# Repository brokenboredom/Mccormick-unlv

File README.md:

Name: Samuel McCormick  
NSHE: 1014303276  
Email: samuel.mccormick@gmail.com

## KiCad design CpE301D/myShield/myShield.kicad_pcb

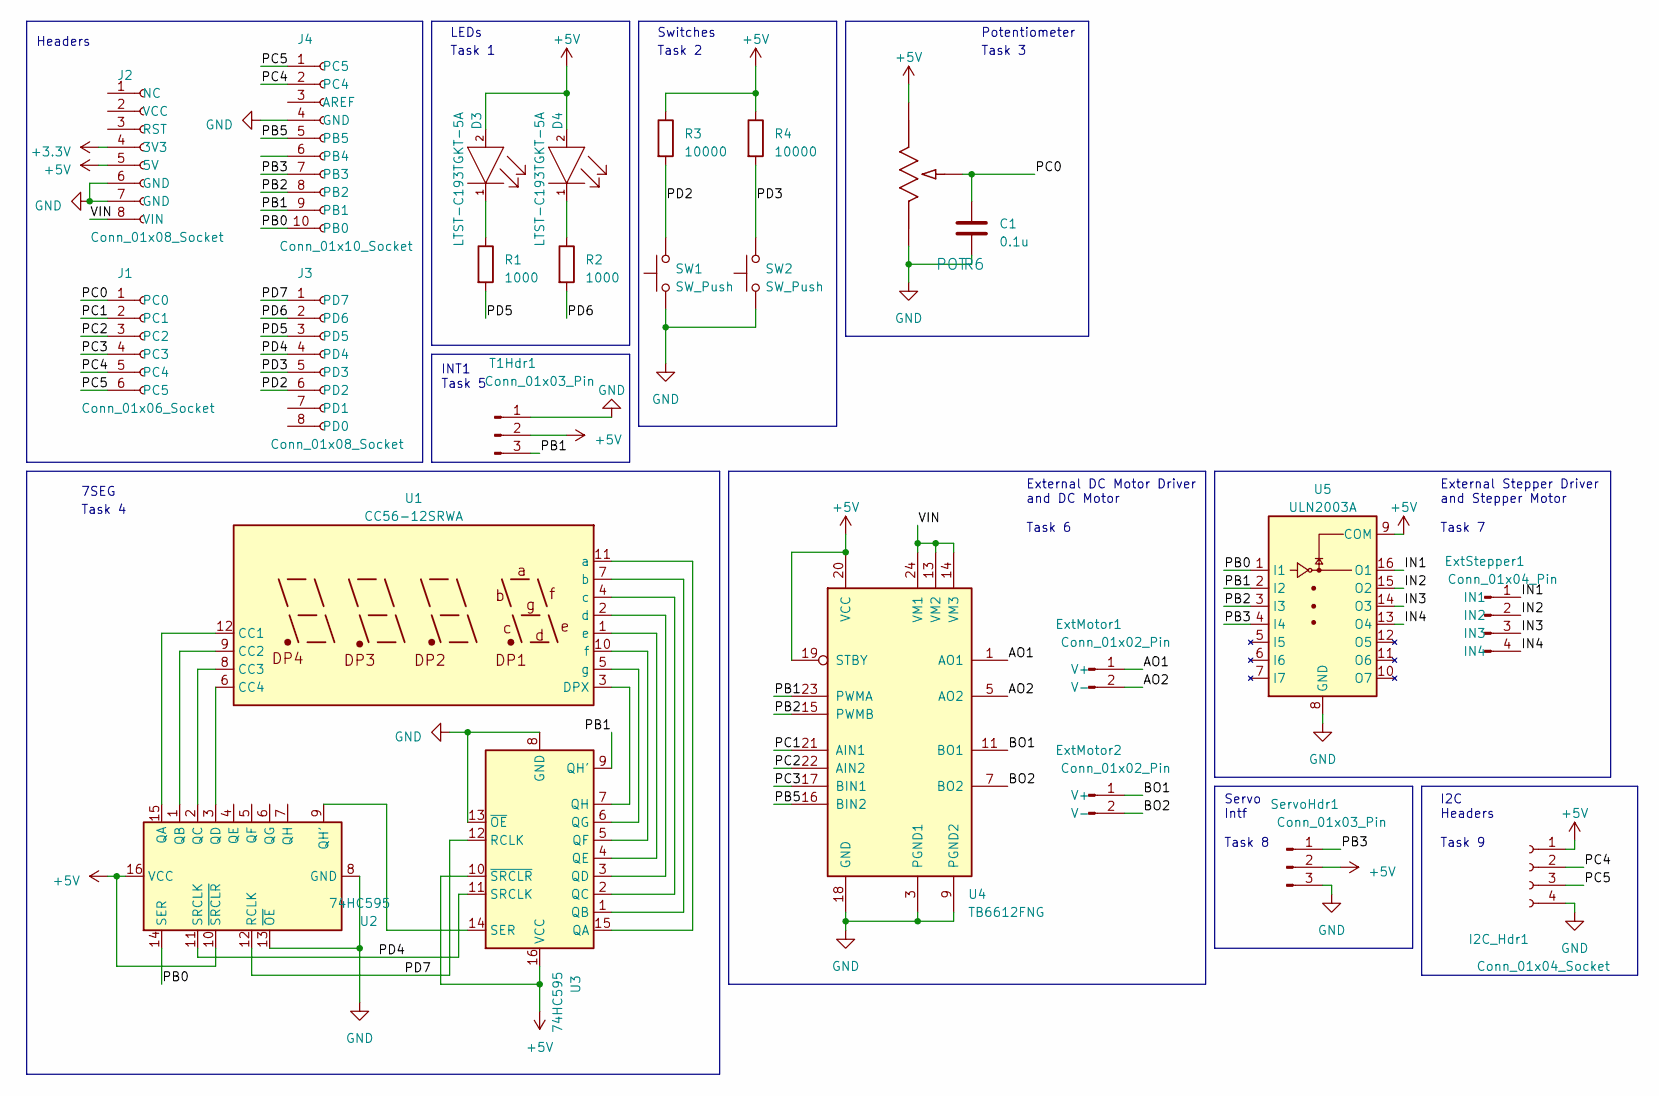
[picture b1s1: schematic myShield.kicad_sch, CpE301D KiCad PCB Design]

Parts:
C1: 0.1u; C_0201_0603Metric
D3, D4: LTST-C193TGKT-5A; Lite-On-LTST-C193TGKT-5A-MFG; forward voltage 3.1V; reverse voltage 5V; mouser part number 859-LTSTC193TGKT5A; digikey description LED GREEN CLEAR CHIP SMD
ExtMotor1, ExtMotor2: Conn_01x02_Pin; PinHeader_1x02_P2.54mm_Vertical
ExtStepper1: Conn_01x04_Pin; PinHeader_1x04_P2.54mm_Vertical
I2C_Hdr1: Conn_01x04_Socket; PinSocket_1x04_P2.54mm_Vertical
J1: Conn_01x06_Socket; PinSocket_1x06_P2.54mm_Vertical
J2, J3: Conn_01x08_Socket; PinSocket_1x08_P2.54mm_Vertical
J4: Conn_01x10_Socket; PinSocket_1x10_P2.54mm_Vertical
R1, R2: 1000; RC0603JR-071KL
R3, R4: 10000; R_0201_0603Metric
R6: POT; 3362P-1-103LF
SW1, SW2: SW_Push; 8-1437565-1
ServoHdr1: Conn_01x03_Pin; PinHeader_1x03_P2.54mm_Vertical
T1Hdr1: Conn_01x03_Pin; PinHeader_1x03_P2.54mm_Vertical
U1: CC56-12SRWA; CA56-12SRWA
U2, U3: 74HC595; SN74HC595DWR
U4: TB6612FNG; TB6612FNG_C_8_EL
U5: ULN2003A

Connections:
+3.3V: J2.4 (3V3)
+5V: D3.2 (ANODE), D4.2 (ANODE), I2C_Hdr1.1, J2.5 (5V), R3.1, R4.1, R6.3, ServoHdr1.2, T1Hdr1.2, U2.10 (~SRCLR), U2.16 (VCC), U3.10 (~SRCLR), U3.16 (VCC), U4.19 (STBY), U4.20 (VCC), U5.9 (COM)
/AO1: ExtMotor1.1 (V+), U4.1 (AO1), U4.2 (AO1)
/AO2: ExtMotor1.2 (V-), U4.5 (AO2), U4.6 (AO2)
/BO1: ExtMotor2.1 (V+), U4.11 (BO1), U4.12 (BO1)
/BO2: ExtMotor2.2 (V-), U4.7 (BO2), U4.8 (BO2)
/IN1: ExtStepper1.1 (IN1), U5.16 (O1)
/IN2: ExtStepper1.2 (IN2), U5.15 (O2)
/IN3: ExtStepper1.3 (IN3), U5.14 (O3)
/IN4: ExtStepper1.4 (IN4), U5.13 (O4)
/PB0: J4.10 (PB0), U2.14 (SER), U5.1 (I1)
/PB1: J4.9 (PB1), T1Hdr1.3, U3.9 (QH'), U4.23 (PWMA), U5.2 (I2)
/PB2: J4.8 (PB2), U4.15 (PWMB), U5.3 (I3)
/PB3: J4.7 (PB3), ServoHdr1.1, U5.4 (I4)
/PB5: J4.5 (PB5), U4.16 (BIN2)
/PC0: C1.1, J1.1 (PC0), R6.2
/PC1: J1.2 (PC1), U4.21 (AIN1)
/PC2: J1.3 (PC2), U4.22 (AIN2)
/PC3: J1.4 (PC3), U4.17 (BIN1)
/PC4: I2C_Hdr1.2, J1.5 (PC4), J4.2 (PC4)
/PC5: I2C_Hdr1.3, J1.6 (PC5), J4.1 (PC5)
/PD2: J3.6 (PD2), R3.2, SW1.2
/PD3: J3.5 (PD3), R4.2, SW2.2
/PD4: J3.4 (PD4), U2.11 (SRCLK), U3.11 (SRCLK)
/PD5: J3.3 (PD5), R1.2
/PD6: J3.2 (PD6), R2.2
/PD7: J3.1 (PD7), U2.12 (RCLK), U3.12 (RCLK)
/VIN: J2.8 (VIN), U4.13 (VM2), U4.14 (VM3), U4.24 (VM1)
GND: C1.2, I2C_Hdr1.4, J2.6 (GND), J2.7 (GND), J4.4 (GND), R6.1, SW1.1, SW2.1, ServoHdr1.3, T1Hdr1.1, U2.8 (GND), U2.13 (~OE), U3.8 (GND), U3.13 (~OE), U4.3 (PGND1), U4.4 (PGND1), U4.9 (PGND2), U4.10 (PGND2), U4.18 (GND), U5.8 (GND)
unnamed: D3.1 (CATHODE), R1.1
unnamed: D4.1 (CATHODE), R2.1
unnamed: U1.12 (CC1), U2.15 (QA)
unnamed: U1.9 (CC2), U2.1 (QB)
unnamed: U1.8 (CC3), U2.2 (QC)
unnamed: U1.6 (CC4), U2.3 (QD)
unnamed: U1.3 (DPX), U3.7 (QH)
unnamed: U1.11 (a), U3.15 (QA)
unnamed: U1.7 (b), U3.1 (QB)
unnamed: U1.4 (c), U3.2 (QC)
unnamed: U1.2 (d), U3.3 (QD)
unnamed: U1.1 (e), U3.4 (QE)
unnamed: U1.10 (f), U3.5 (QF)
unnamed: U1.5 (g), U3.6 (QG)
unnamed: U2.9 (QH'), U3.14 (SER)

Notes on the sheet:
External DC Motor Driver and DC Motor Task 6
Switches
Task 2
Servo Intf Task 8
Task 3
7SEG
I2C Headers Task 9
Potentiometer
External Stepper Driver and Stepper Motor Task 7
INT1 Task 5
Task 4
Headers
Task 1
LEDs

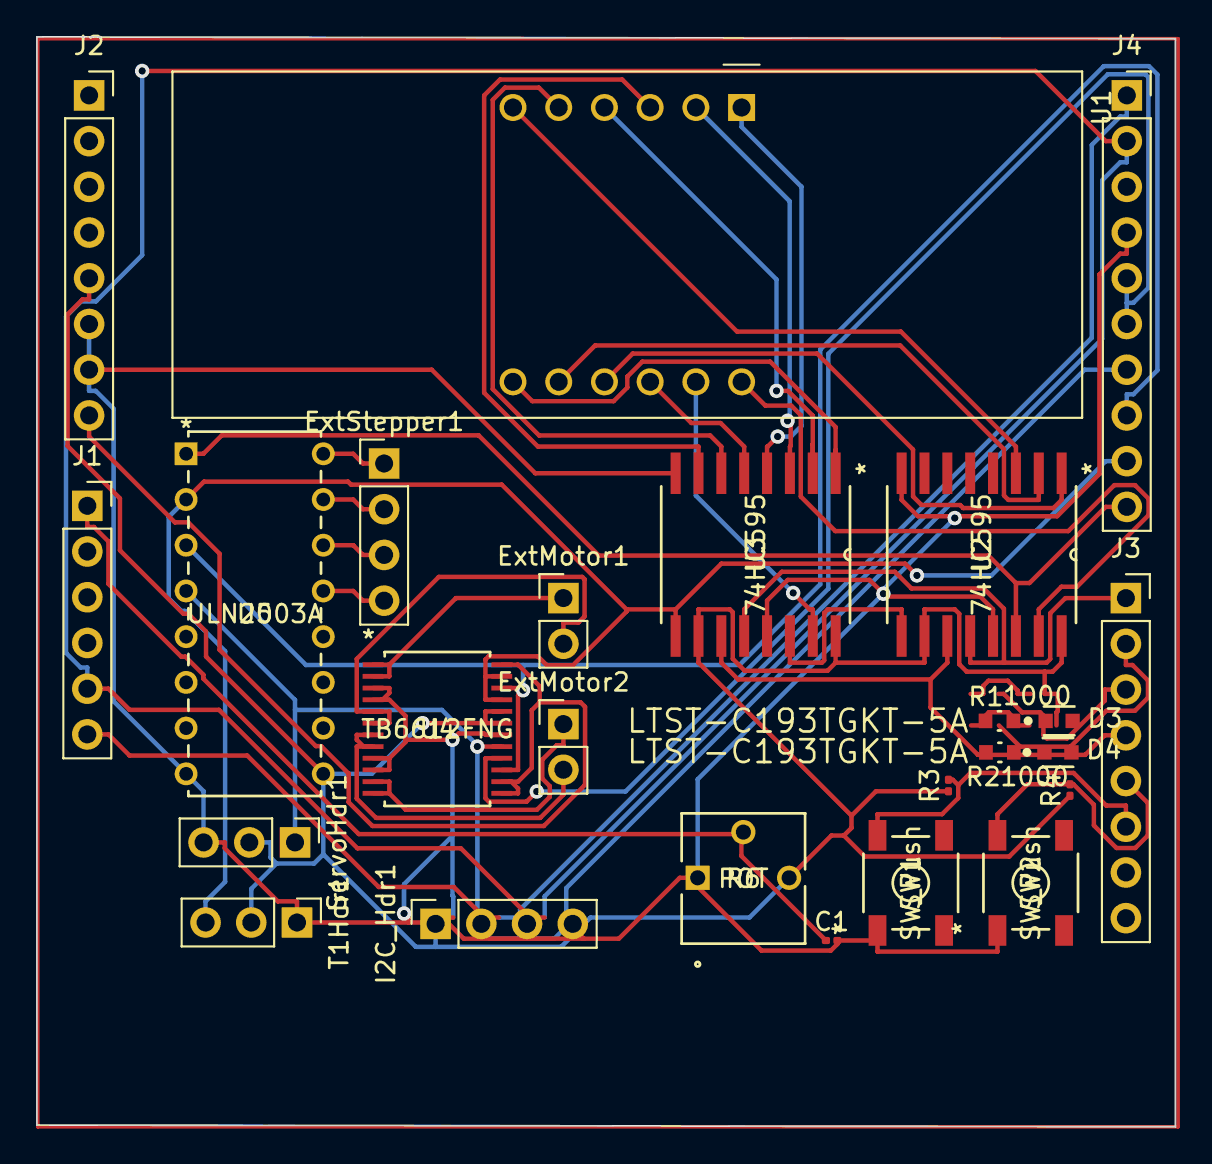
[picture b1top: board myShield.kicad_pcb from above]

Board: 2 copper layers, 63.2 x 60.5 mm, 25 parts (0 on the bottom side), 43 nets.

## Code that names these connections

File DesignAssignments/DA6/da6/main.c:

/*
 * da6.c
 *
 * Created: 4/13/2023 7:54:39 AM
 * Author : samue
 */ 

//-------------------------------------------------------------------------
#define F_CPU 16000000UL

#include <avr/io.h>
#include <util/delay.h>
#include <avr/interrupt.h>
#include <stdio.h>
#define BAUDRATE 9600
#define BAUD_PRESCALLER (((F_CPU / (BAUDRATE * 16UL))) - 1)
//-------------------------------------------------------------------------------

#define SHIFT_REGISTER DDRB
#define SHIFT_PORT PORTB
#define DATA (1<<PB3)		//MOSI (SI)
#define LATCH (1<<PB2)		//SS   (RCK)
#define CLOCK (1<<PB5)		//SCK  (SCK)

void read_adc(void);
void adc_init(void);
void init_IO(void){
	//Setup IO
	SHIFT_REGISTER |= (DATA | LATCH | CLOCK);	//Set control pins as outputs
	SHIFT_PORT &= ~(DATA | LATCH | CLOCK);		//Set control pins low
}
void init_SPI(void){
	//Setup SPI
	SPCR = (1<<SPE) | (1<<MSTR);	//Start SPI as Master
}
void spi_send(unsigned char byte){
	SPDR = byte;			//Shift in some data
	while(!(SPSR & (1<<SPIF)));	//Wait for SPI process to finish
}

/* Segment byte maps for numbers 0 to 9 */
const uint8_t SEGMENT_MAP[] = {0xC0, 0xF9, 0xA4, 0xB0, 0x99,
									0x92, 0x82, 0xF8, 0X80, 0X90};
/* Byte maps to select digit 1 to 4 */
const uint8_t SEGMENT_SELECT[] = {0xF1, 0xF2, 0xF4, 0xF8};
	
volatile unsigned int adc_temp;
volatile unsigned int adc_hundreds;
volatile unsigned int adc_tens;
volatile unsigned int adc_ones;
volatile int j = 4;

int main(void)
{
    //Configure TIMER2
	TCCR0A |=	(1 << COM0B1) |								// Fast PWM mode non-inverting (OC0B )
				(1 << WGM01) | (1 << WGM00);				// Fast PWM, TOP: 0xFF
	TCCR0B |=	(1 << CS02) | (1 << CS01) | (1 << CS00);	// 1024 prescaler

	//Motor test configure
	DDRD |= 0x03;		// PORTD 0 and 1 as Output
	DDRD |= (1<<PD5);	// PD5(OC0B) motor enable
	PORTD = 0x01;		// set motor to run
    adc_init();			// Initialize ADC
	init_IO();			// Setup IO ports
	init_SPI();			// Initialize SPI as master
    ADCSRA |= (1<<ADSC); //trigger
    _delay_ms(125);
    sei();				// set global interrupts

    while (1) {
	    

    }
}



void adc_init(void)
{
	ADMUX |= (0 << REFS1) |  // Voltage reference bits
	(1 << REFS0) |
	(0 << ADLAR) |  // Left adjust
	(0 << MUX3 ) |  // Source selector
	(0 << MUX2) |
	(0 << MUX1) |	// Select ADC0 (PC0) also our POT
	(0 << MUX0);
	ADCSRA |= (1 << ADEN) | //Enable ADC
	(0 << ADSC) |           //Start conversion
	(1 << ADATE) |          //Enable auto trigger
	(0 << ADIF) |           //Interrupt flag
	(1 << ADIE) |           //Enable interrupt
	(1 << ADPS2) |          //Prescalar
	(0 << ADPS1) |
	(1 << ADPS0);
	ADCSRB |= (0 << ADTS2) |  //Auto-trigger source
	(0 << ADTS1) |
	(0 << ADTS0);
}

//ADC conversion complete ISR
ISR(ADC_vect)
{
	adc_temp += ADC; //sum
	j--;
	if (j==1)
	{
		adc_temp /= 16; // 0-1023 / 16 = 0-255 / 4 average
		// This adc value from POT on protoshield should set our DC PWM duty cycle
		// So this reading needs to be translated to OCR1A
		OCR0B = adc_temp;	// Overflow will just start from 0%
		adc_temp = 0;
		j = 4;

		//Pull LATCH low (Important: this is necessary to start the SPI transfer!)
		SHIFT_PORT &= ~LATCH;

		// Extract our ADC digits
		adc_hundreds = adc_temp % 100;
		adc_temp = adc_temp - (adc_hundreds * 100)
		adc_tens = adc_temp % 10;
		adc_temp = adc_temp - (adc_tens * 10)
		adc_ones = adc_temp
		spi_send((unsigned char)SEGMENT_MAP[adc_hundreds]);
		spi_send((unsigned char)0xF2);
		spi_send((unsigned char)SEGMENT_MAP[adc_tens]);
		spi_send((unsigned char)0xF4);
		spi_send((unsigned char)SEGMENT_MAP[adc_ones]);
		spi_send((unsigned char)0xF8);
		//Toggle latch to copy data to the storage register
		SHIFT_PORT |= LATCH;
		SHIFT_PORT &= ~LATCH;
		//wait for a little bit before repeating everything
		_delay_ms(125);
	}
}

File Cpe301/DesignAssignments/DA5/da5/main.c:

/*
 * da5.c
 *
 * Created: 4/12/2023 5:50:19 PM
 * Author : Samuel McCormick
 */ 
//-------------------------------------------------------------------------
#define F_CPU 16000000UL

#include <stdio.h>
#include <stdlib.h>
#include <avr/io.h>
#include <util/delay.h>
#include <avr/interrupt.h>
#include <string.h>

#define BAUDRATE 9600
#define BAUD_PRESCALLER (((F_CPU / (BAUDRATE * 16UL))) - 1)
//-------------------------------------------------------------------------------

#define  Trigger_pin	PB5			// Trigger pin

int TimerOverflow = 0;				// counts overflows

volatile uint16_t tempCnt = 250;	// holds TCNT1 for US sensor
volatile uint16_t distance = 0;		// holds distance from echo calculation
volatile int servoCnt = 97;			// holds OCR1A for servo
volatile uint16_t degree = 0;		// holds approx. angle

void USART_init(void){
	
	UBRR0H = (uint8_t)(BAUD_PRESCALLER>>8);
	UBRR0L = (uint8_t)(BAUD_PRESCALLER);
	UCSR0B = (1<<RXEN0)|(1<<TXEN0);
	UCSR0C = (3<<UCSZ00);
}

void USART_send( unsigned char data){
	
	while(!(UCSR0A & (1<<UDRE0)));
	UDR0 = data;
	
}

void USART_putstring(char* StringPtr){
	
	while(*StringPtr != 0x00){
		USART_send(*StringPtr);
	StringPtr++;}
	
}

ISR(TIMER1_OVF_vect)
{
	TimerOverflow++;		/* Increment Timer Overflow count */
}

int main(void)
{
	char string[10];
	char angle[10];
	long count;
	double distance;

	DDRB|=(1<<PB1);				// PWM Pins as Out	
	DDRB |= (1<<Trigger_pin);	// Make trigger pin as output, PB0 is echo
	
	USART_init();
	
	sei();						/* Enable global interrupt */


	//--------------------------------------------
	
	while(1)
	{
		
		// -- DO Servo operation
		//--------------------------------------------
		//Servo motor operations
	
		//Configure TIMER1
		TCCR1A|=(1<<COM1A1)|(1<<COM1B1)|(1<<WGM11);			// NON Inverted PWM
		TCCR1B|=(1<<WGM13)|(1<<WGM12)|(1<<CS11)|(1<<CS10);	// PRESCALER=64 MODE 14(FAST PWM)
		TIMSK1 &= ~(1 << TOIE1);							// Disable Timer1 overflow interrupts

		ICR1=4999;											// 16MHz/64/4999 = fPWM=50Hz (Period = 20ms Standard).
		//--------------------------------------------
		// 535 = 180 degrees
		if(servoCnt > 535) {
			servoCnt = 97; // 0 degrees
			OCR1A = servoCnt;
			degree = 0;
			_delay_ms(100);
		}
		else {
			OCR1A = servoCnt;
			/*******************************************************/
			degree = degree + 2;
			servoCnt += 5;			// 535/97 = 438. 438/(180/2) ~6. 438/(180/2.5) ~= 4. We'll use 5 for ~87 segments
			_delay_ms(500);
		}
		
		// -- DO Sonic operation
		TIMSK1 = (1 << TOIE1);			// Enable Timer1 overflow interrupts
		TCCR1A = 0;						// Set all bit to zero Normal operation

		PORTB |= (1 << Trigger_pin);	// Give 10us trigger pulse on trig. pin to HC-SR04
		_delay_us(10);
		PORTB &= (~(1 << Trigger_pin));
		
		TCNT1 = 0;			// Clear Timer counter
		TCCR1B = 0x41;		// Setting for capture rising edge, No pre-scaler
		TIFR1 = 1<<ICF1;	// Clear ICP flag (Input Capture flag)
		TIFR1 = 1<<TOV1;	// Clear Timer Overflow flag

		// Calculate width of Echo by Input Capture (ICP) on PortD PD6
		
		while ((TIFR1 & (1 << ICF1)) == 0);		// Wait for rising edge
		TCNT1 = 0;								// Clear Timer counter
		TCCR1B = 0x01;							// Setting for capture falling edge, No pre-scaler
		TIFR1 = 1<<ICF1;						// Clear ICP flag (Input Capture flag)
		TIFR1 = 1<<TOV1;						// Clear Timer Overflow flag
		TimerOverflow = 0;						// Clear Timer overflow count

		while ((TIFR1 & (1 << ICF1)) == 0);		// Wait for falling edge
		count = ICR1 + (65535 * TimerOverflow);	// Take value of capture register
		
		// 8MHz Timer freq, sound speed =343 m/s, calculation mentioned in doc.
		distance = (double)count / (58*16);
		// Output should look like: "angle,distance."
		itoa(degree, angle, 10);			// String to Int angle for Processor graph
		USART_putstring(angle);				
		USART_putstring(",");				// add the comma
		itoa(distance, string, 10);			// String to int distance
		USART_putstring(string);
		USART_putstring(".");				// add ending period
		_delay_ms(10);
		
	}
}

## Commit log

2023-03-20 DA3 complete
    DA3 showing 3 asynchronous timers/leds. Includes solution, report, youtube.
2023-03-20 Updated pdf
    Included waveform
2023-03-20 Updated pdf
    included kicad schematic
2023-03-30 DA4 Uploaded. PDF/sol/vid
    Uploaded full solution folder, pdf report, and video link
2023-04-13 Added DA5 - full
    Full upload of DA5 with code, report, demo links, and schematic DA5/da5/kicad
2023-04-17 DA6 partial upload.
    Part 1 complete. Part 2 no work. Part 3 partial.
2023-04-30 Uploaded DA7
    Split into task 1/2/3. Contains code, report, and schematics
2023-05-09 PCB Design - myShield
    Full upload of CpE301D PCB design. Includes schematics, gerber, additional libraries, 3d captures, and report.
2023-09-24 Reorganized files into respective classes
    Needed a section for cpe400 so reorganized main branch by course
2023-09-25 Rename Cpe400 > Cpe403
    Rename Cpe400 > Cpe403
2023-10-14 Assignment 1 full upload
    Upload of all assignment 1 tasks, report, and text file. Including source code
2023-11-09 DA2 implemented. Incomplete.
    Joystick and PWM working. QEI configured but not implemented. Motor not being driven by chip.
2023-12-02 What i have for DA3 incomplete
    Uploading what I have finished so far. HWI and Display were causing an exception and I don't know why and I don't know how I fixed it but I spent hours fumbling around with them.
2023-12-02 Completed DA3
    After much crashing and problems with the clock and semaphore scope I am uploading the complete project with report and youtube links
2023-12-14 Never pushed this
    Assignment 4 working to the best of my ability with a board malfunction but ultimately incomplete
2023-12-14 Uploaded phone app captures
    Phone captures for app showing incorrect Service display but correct advertisement data. Won't connect to the service.

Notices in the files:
parts and their libraries:
Copyright 2016 Accelerated Designs. All rights reserved.
